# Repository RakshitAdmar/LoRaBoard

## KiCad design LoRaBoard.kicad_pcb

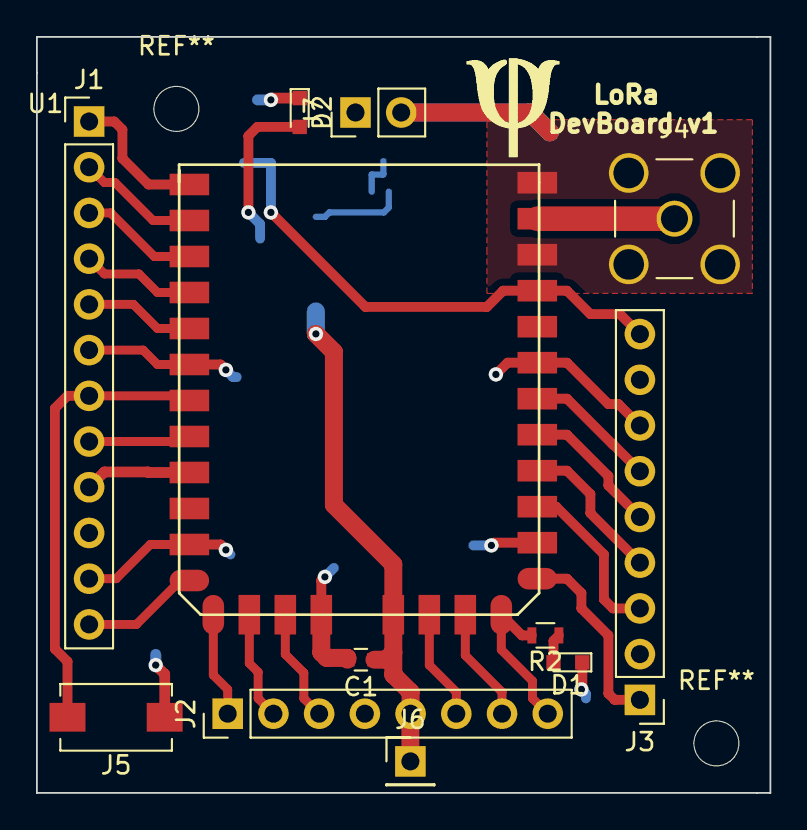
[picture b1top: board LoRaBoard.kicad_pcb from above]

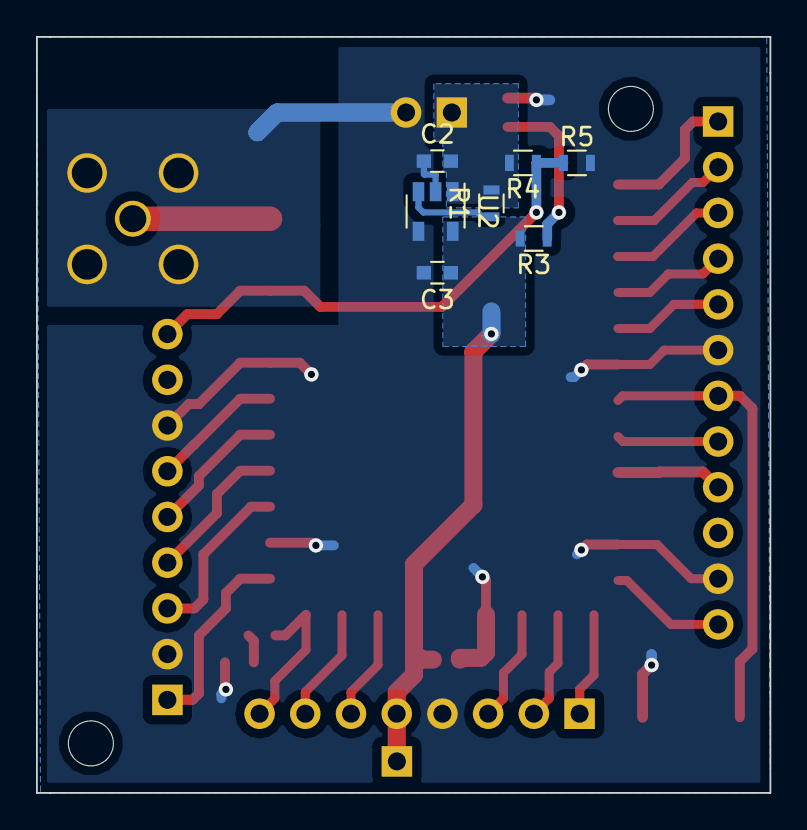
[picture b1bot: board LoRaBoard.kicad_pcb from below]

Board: 2 copper layers, 40.8 x 42.0 mm, 20 parts (7 on the bottom side), 28 nets.

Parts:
C1: 0.1u; C_0603
C2, C3: 1u; C_0603
D1, D2: LED; LED_0603
J1: CONN_01X12; Pin_Header_Straight_1x12_Pitch2.54mm
J2: CONN_01X08; Pin_Header_Straight_1x08_Pitch2.54mm
J3: CONN_01X09; Pin_Header_Straight_1x09_Pitch2.54mm
J4: CONN_COAXIAL; SMA_THT_Jack_Straight
J5: SwitchSPST; SW_SPST_EVQPE1
J6: CONN_01X01; Pin_Header_Straight_1x01_Pitch2.54mm
J7: PWR; Pin_Header_Straight_1x02_Pitch2.54mm
LOGO: logo
R1, R2, R3, R5: 10k; R_0603
R4: 33k; R_0603
U1: im880b
U2: LDO-TPS78233; SOT-23-5

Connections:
+3V3: C1.1, C3.1, J2.5, J6.1, R3.2, U1.17, U2.5
+BATT: C2.2, J7.1, R1.2, R4.2, U2.1
/1: J1.1, U1.1
/2: J1.2, U1.2
/3: J1.3, U1.3
/4: J1.4, U1.4
/5: J1.5, U1.5
/7: J1.7, J5.2, U1.7
/8: J1.8, U1.8
/9: J1.9, U1.9
/12: J1.12, U1.12
/13: J2.1, U1.13
/14: J2.2, U1.14
/15: J2.3, U1.15
/18: J2.6, U1.18
/19: J2.7, U1.19
/20: J2.8, R2.2, U1.20
/21: J3.1, U1.21
/23: J3.3, U1.23
/24: J3.4, U1.24
/25: J3.5, U1.25
/26: J3.6, U1.26
/29: J3.9, R4.1, R5.1, U1.29
/RF: J4.1, U1.31
GND: C1.2, C2.1, C3.2, D1.1, D2.1, J1.6, J1.11, J2.4, J3.2, J3.7, J4.2, J5.1, J7.2, R5.2, U1.6, U1.11, U1.16, U1.22, U1.27, U1.30, U1.32, U2.2, U2.4
unnamed: D1.2, R2.1
unnamed: D2.2, R3.1
unnamed: R1.1, U2.3

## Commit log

2017-03-22 Started LoRa board project
2017-03-27 PCB layout
2017-03-30 60% complete
2017-04-03 LoRaBoard Done
2017-04-04 Done, panelize
2017-04-05 Panel added
2017-04-06 Done
2017-04-09 PCB complete, panel complete
2017-04-10 Panelization done, send for Fab
